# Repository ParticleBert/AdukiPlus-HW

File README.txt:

AdukiPlus-HW

The hardware for the AdukiPlus-Project as schematic and board file for EAGLE.

The design is based on an Atmel ATtiny24/44/84 microcontroller. As current source for the
LEDs works an AMS 3691. The LEDs are Luxeon Rebel.

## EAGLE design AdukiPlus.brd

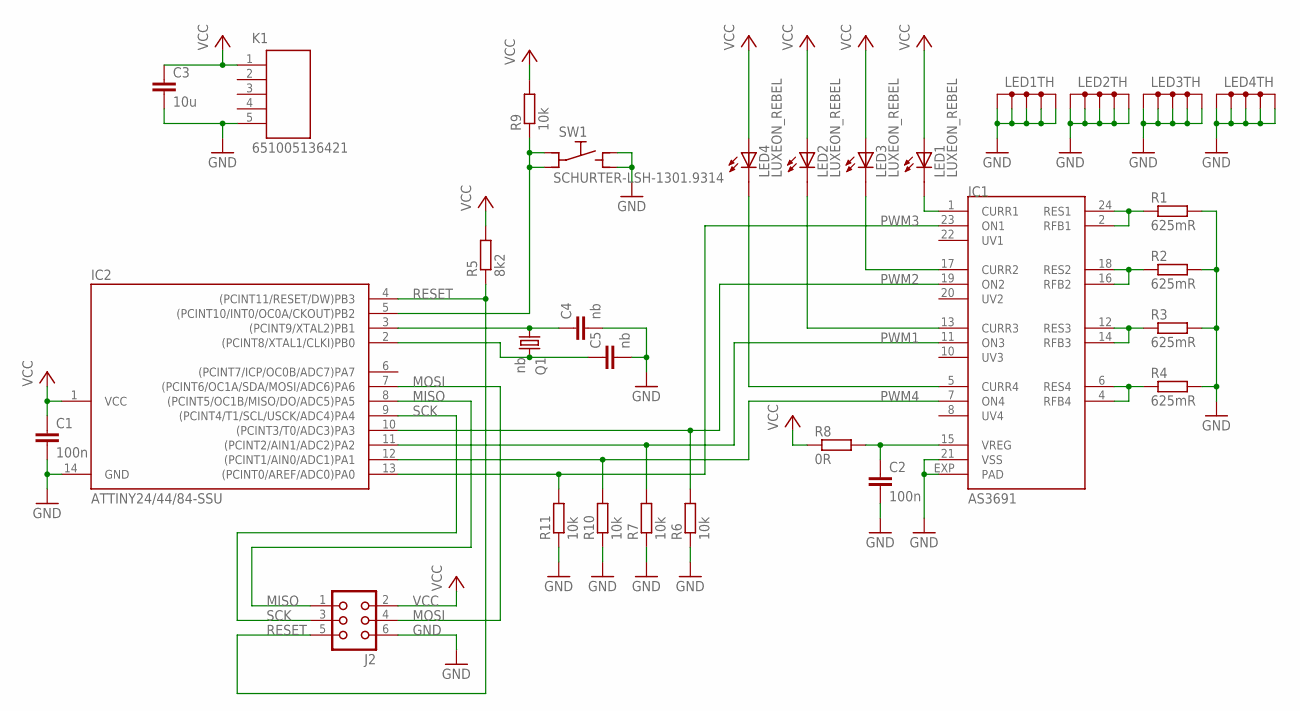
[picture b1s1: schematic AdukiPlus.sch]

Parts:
C1, C2: 100n; C0603
C3: 10u; C0603
C4, C5: nb; C0603
IC1: AS3691; QFN24-4X4
IC2: ATTINY24/44/84-SSU; SOIC14
J2: CON06
K1: 651005136421
LED1, LED2, LED3, LED4: LUXEON_REBEL
Q1: nb; 32X25
R1, R2, R3, R4: 625mR; R0603
R5: 8k2; R0603
R6, R7, R9, R10, R11: 10k; R0603
R8: 0R; R0603
SW1: SCHURTER-LSH-1301.9314; LSH

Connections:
GND: C1.2, C2.2, C3.2, C4.2, C5.2, IC1.21 (VSS), IC1.EXP (PAD), IC2.14 (GND), J2.6, K1.5, LED1.TH, LED1.TH@1 (TH), LED1.TH@2 (TH), LED1.TH@3 (TH), LED1.TH@4 (TH), LED2.TH, LED2.TH@1 (TH), LED2.TH@2 (TH), LED2.TH@3 (TH), LED2.TH@4 (TH), LED3.TH, LED3.TH@1 (TH), LED3.TH@2 (TH), LED3.TH@3 (TH), LED3.TH@4 (TH), LED4.TH, LED4.TH@1 (TH), LED4.TH@2 (TH), LED4.TH@3 (TH), LED4.TH@4 (TH), R1.2, R2.2, R3.2, R4.2, R6.1, R7.1, R10.1, R11.1, SW1.NO1 (NO), SW1.NO2 (NO)
MISO: IC2.8 ((PCINT5/OC1B/MISO/DO/ADC5)PA5), J2.1
MOSI: IC2.7 ((PCINT6/OC1A/SDA/MOSI/ADC6)PA6), J2.4
unnamed: IC1.2 (RFB1), IC1.24 (RES1), R1.1
unnamed: IC1.16 (RFB2), IC1.18 (RES2), R2.1
unnamed: IC1.12 (RES3), IC1.14 (RFB3), R3.1
unnamed: IC1.4 (RFB4), IC1.6 (RES4), R4.1
unnamed: IC1.1 (CURR1), LED1.C
unnamed: IC1.13 (CURR3), LED2.C
unnamed: IC1.17 (CURR2), LED3.C
unnamed: IC1.5 (CURR4), LED4.C
unnamed: IC2.5 ((PCINT10/INT0/OC0A/CKOUT)PB2), R9.1, SW1.C1 (C), SW1.C2 (C)
unnamed: C2.1, IC1.15 (VREG), R8.2
unnamed: C4.1, IC2.3 ((PCINT9/XTAL2)PB1), Q1.1
unnamed: C5.1, IC2.2 ((PCINT8/XTAL1/CLKI)PB0), Q1.3 (2)
PWM1: IC1.11 (ON3), IC2.11 ((PCINT2/AIN1/ADC2)PA2), R7.2
PWM2: IC1.19 (ON2), IC2.10 ((PCINT3/T0/ADC3)PA3), R6.2
PWM3: IC1.23 (ON1), IC2.13 ((PCINT0/AREF/ADC0)PA0), R11.2
PWM4: IC1.7 (ON4), IC2.12 ((PCINT1/AIN0/ADC1)PA1), R10.2
RESET: IC2.4 ((PCINT11/RESET/DW)PB3), J2.5, R5.1
SCK: IC2.9 ((PCINT4/T1/SCL/USCK/ADC4)PA4), J2.3
VCC: C1.1, C3.1, IC2.1 (VCC), J2.2, K1.1, LED1.A, LED2.A, LED3.A, LED4.A, R5.2, R8.1, R9.2

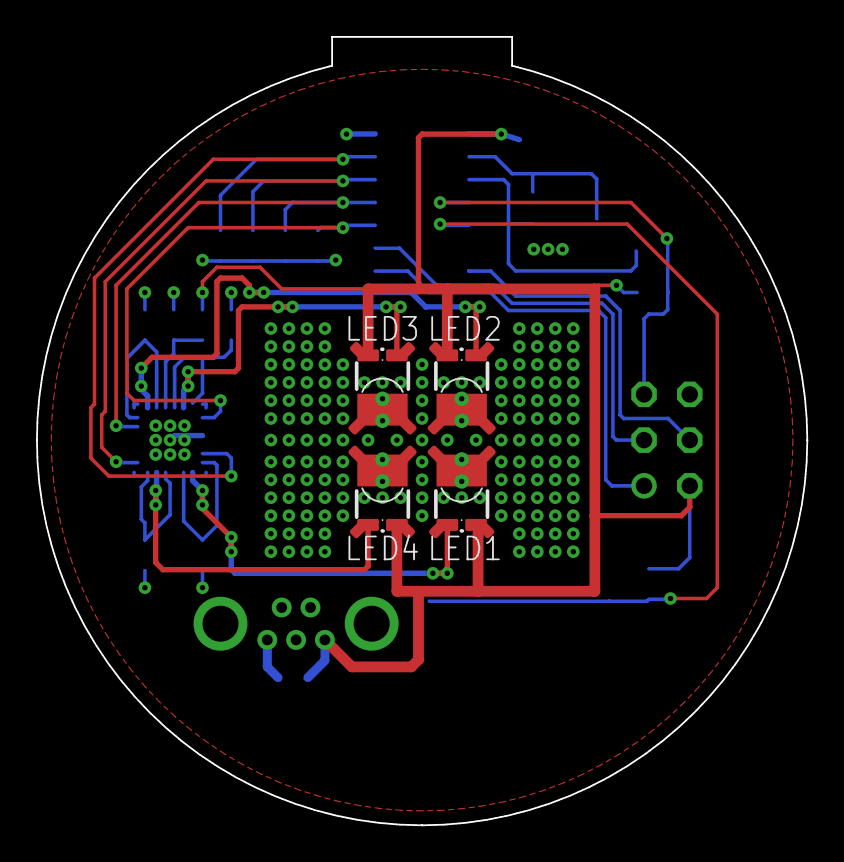
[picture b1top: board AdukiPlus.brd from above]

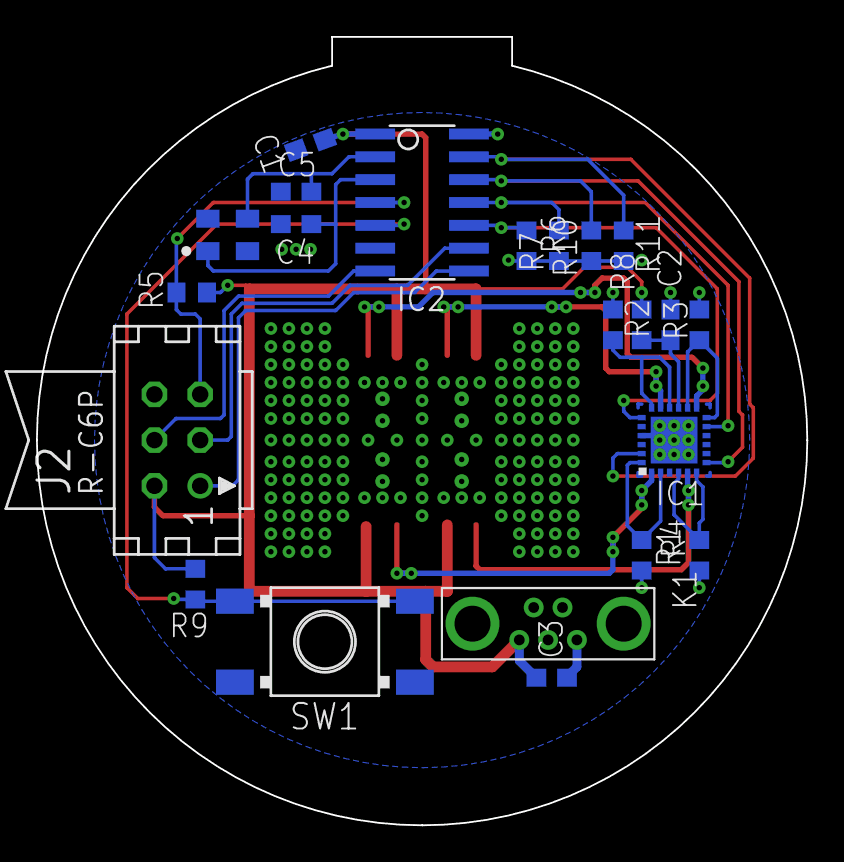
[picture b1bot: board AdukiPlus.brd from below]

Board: 2 copper layers, 42.8 x 43.8 mm, 26 parts (22 on the bottom side), 22 nets.

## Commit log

2013-02-03 Initial Release
    A snapshot of the working and tested hardware.

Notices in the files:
parts and their libraries:
Wuerth_Elektronik_eiCan_11_Communication: Copyright: Würth Elektronik
